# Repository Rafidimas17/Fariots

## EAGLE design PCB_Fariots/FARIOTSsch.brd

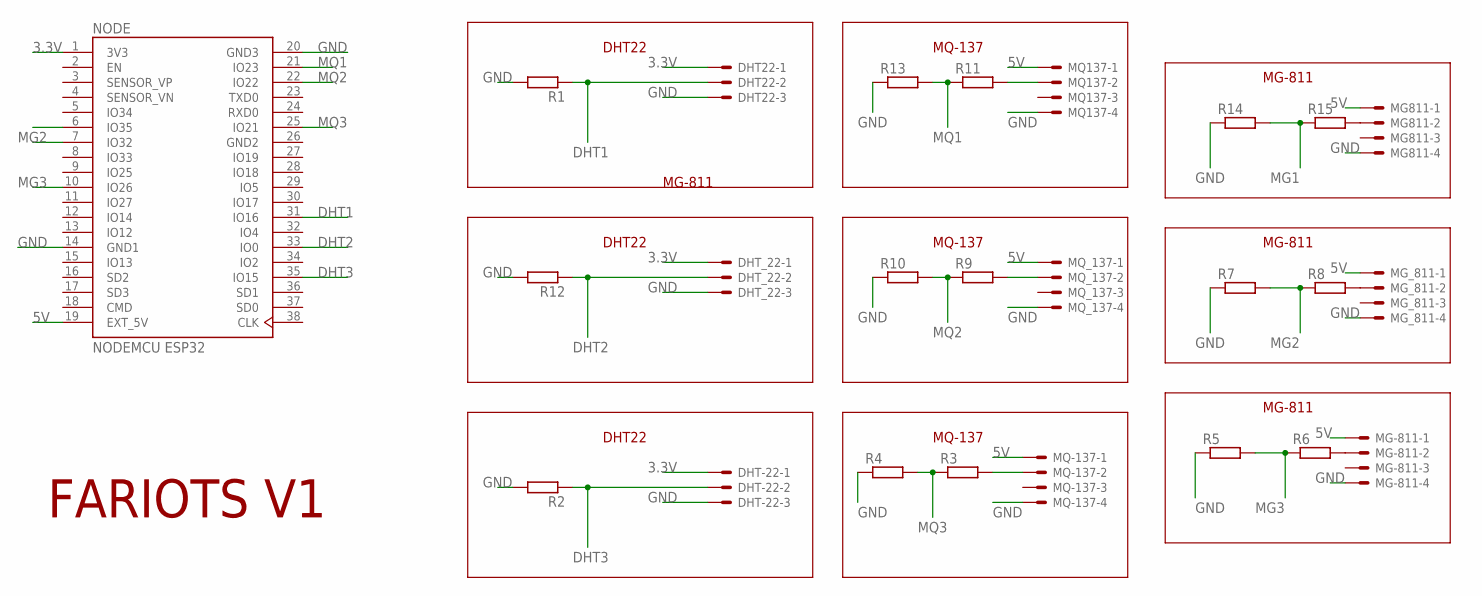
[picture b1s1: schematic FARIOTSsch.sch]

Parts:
DHT22: C-GRID-03-70543; 70543-03
DHT-22: C-GRID-03-70543; 70543-03
DHT_22: C-GRID-03-70543; 70543-03
MG811: C-GRID-04-70543; 70543-04
MG-811: C-GRID-04-70543; 70543-04
MG_811: C-GRID-04-70543; 70543-04
MQ137: C-GRID-04-70543; 70543-04
MQ-137: C-GRID-04-70543; 70543-04
MQ_137: C-GRID-04-70543; 70543-04
NODE: NODEMCU ESP32; MODULE_ESP32-DEVKITC-32D
R1, R2, R3, R4, R5, R6, R7, R8, R9, R10, R11, R12, R13, R14, R15: R-EU_0204/7; 0204/7

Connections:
3.3V: DHT22.1, DHT-22.1, DHT_22.1, NODE.1 (3V3)
5V: MG811.1, MG-811.1, MG_811.1, MQ137.1, MQ-137.1, MQ_137.1, NODE.19 (EXT_5V)
DHT1: DHT22.2, NODE.31 (IO16), R1.1
DHT2: DHT_22.2, NODE.33 (IO0), R12.1
DHT3: DHT-22.2, NODE.35 (IO15), R2.1
GND: DHT22.3, DHT-22.3, DHT_22.3, MG811.4, MG-811.4, MG_811.4, MQ137.4, MQ-137.4, MQ_137.4, NODE.14 (GND1), NODE.20 (GND3), R1.2, R2.2, R4.1, R5.1, R7.1, R10.1, R12.2, R13.1, R14.1
GND2: NODE.26 (GND2)
MG1: NODE.6 (IO35), R14.2, R15.1
MG2: NODE.7 (IO32), R7.2, R8.1
MG3: NODE.10 (IO26), R5.2, R6.1
MQ1: NODE.21 (IO23), R11.1, R13.2
MQ2: NODE.22 (IO22), R9.1, R10.2
MQ3: NODE.25 (IO21), R3.1, R4.2
unnamed: MG-811.2, R6.2
unnamed: MQ-137.2, R3.2
unnamed: MG_811.2, R8.2
unnamed: MQ_137.2, R9.2
unnamed: MQ137.2, R11.2
unnamed: MG811.2, R15.2

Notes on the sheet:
MG-811
MQ-137
DHT22
FARIOTS V1

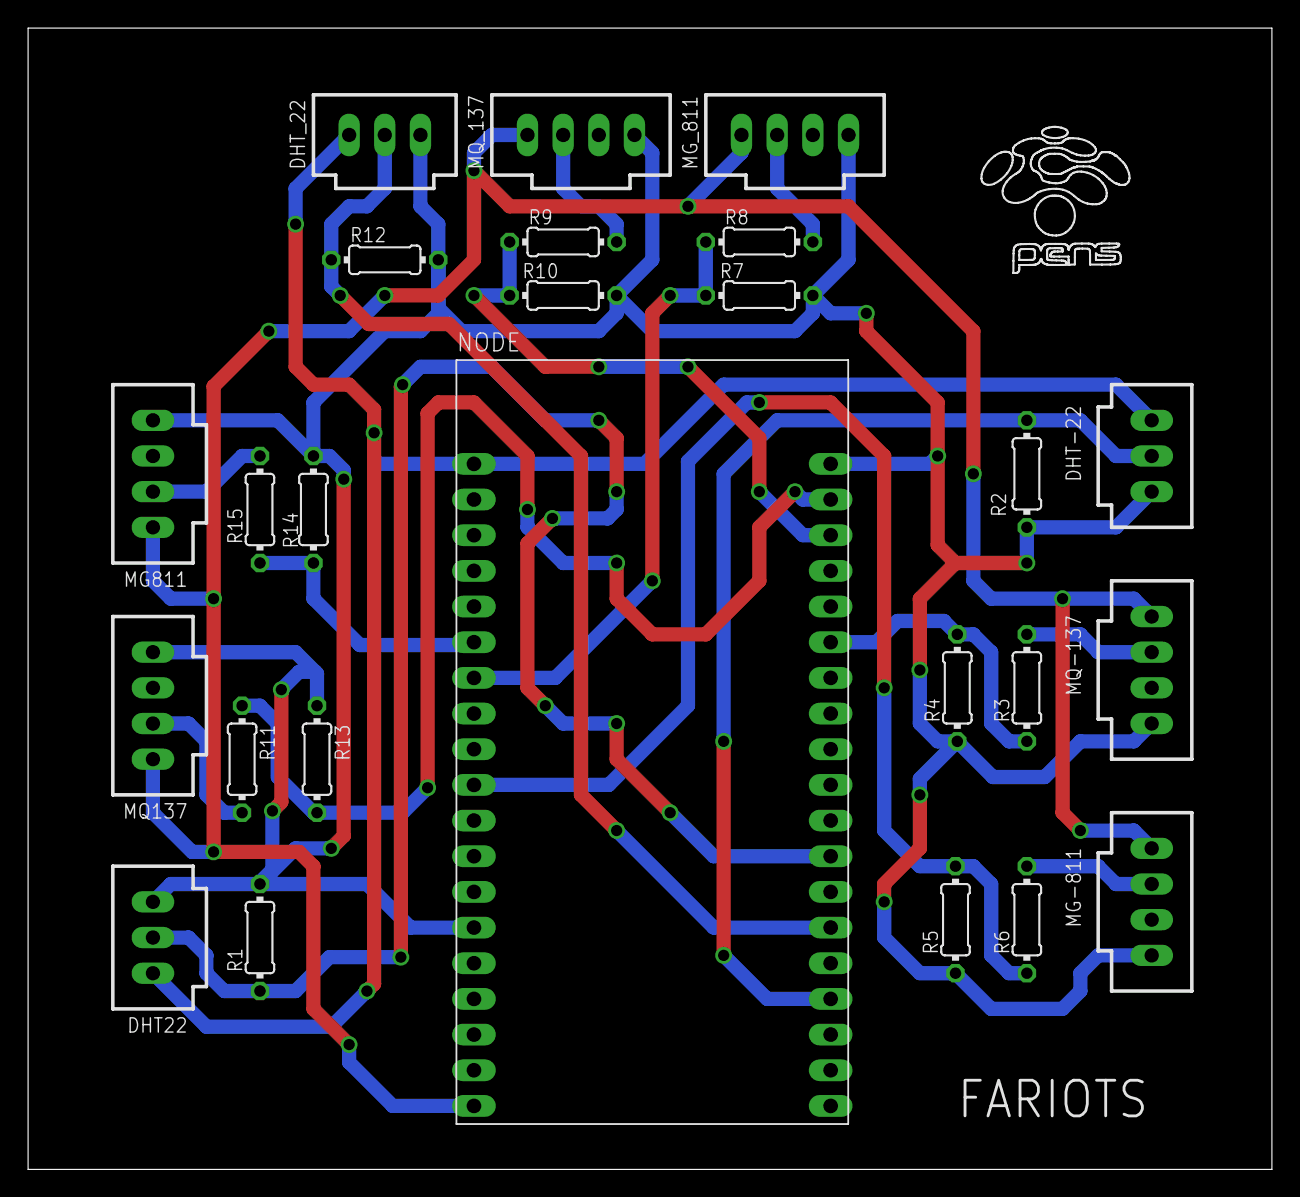
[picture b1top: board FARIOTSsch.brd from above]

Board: 2 copper layers, 88.6 x 81.3 mm, 25 parts (0 on the bottom side), 18 nets.

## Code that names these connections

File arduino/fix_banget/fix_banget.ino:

#include <WiFi.h>
#include "CO2Sensor.h"
#include <DHT.h>

//sediakan var untuk DHT
#define DHTPIN1 16
#define DHTPIN2 0
#define DHTPIN3 15
#define DHTTYPE DHT22
#define RL 47  //The value of resistor RL is 47K
#define m -0.263 //Enter calculated Slope 
#define b 0.42 //Enter calculated intercept
#define Ro 20 //Enter found Ro value
#define AN_Pot1    34 //Sensor is connected to 34
#define AN_Pot2    33 //Sensor is connected to 33
#define AN_Pot3    25 //Sensor is connected to 25

CO2Sensor co2Sensor(35, 0.99, 100);
CO2Sensor co2Sensor2(32, 0.99, 100);
CO2Sensor co2Sensor3(26, 0.99, 100);
//sediakan sebuah object untuk DHT22
DHT dht1(DHTPIN1, DHTTYPE);
DHT dht2(DHTPIN2, DHTTYPE);
DHT dht3(DHTPIN3, DHTTYPE);
const char* ssid     = "Aay";
const char* password = "hahgimana";
const char* host = "fariots.com";

void setup()
{
  dht1.begin();
  dht2.begin();
  dht3.begin();
  co2Sensor.calibrate();
  co2Sensor2.calibrate();
  co2Sensor3.calibrate();
  Serial.begin(115200);

  // We start by connecting to a WiFi network

//  Serial.println();
//  Serial.println();
//  Serial.print("Connecting to ");
//  Serial.println(ssid);

  WiFi.begin(ssid, password);

  while (WiFi.status() != WL_CONNECTED) {
    delay(500);
//    Serial.print(".");
  }

//  Serial.println("");
//  Serial.println("WiFi connected");
//  Serial.println("IP address: ");
//  Serial.println(WiFi.localIP());
}



void loop()
{
//mq1
  float VRL; //Voltage drop across the MQ sensor
  float Rs; //Sensor resistance at gas concentration 
  float ratio; //Define variable for ratio

  VRL = analogRead(AN_Pot1)*(5.0/1023.0); //Measure the voltage drop and convert to 0-5V
  Rs = ((5.0*RL)/VRL)-RL; //Use formula to get Rs value
  ratio = Rs/Ro;  // find ratio Rs/Ro

//mq2
  float VRL2; //Voltage drop across the MQ sensor
  float Rs2; //Sensor resistance at gas concentration 
  float ratio2; //Define variable for ratio

  VRL2 = analogRead(AN_Pot2)*(5.0/1023.0); //Measure the voltage drop and convert to 0-5V
  Rs2 = ((5.0*RL)/VRL2)-RL; //Use formula to get Rs value
  ratio2 = Rs2/Ro;  // find ratio Rs/Ro

  //mq3
  float VRL3; //Voltage drop across the MQ sensor
  float Rs3; //Sensor resistance at gas concentration 
  float ratio3; //Define variable for ratio

  VRL3 = analogRead(AN_Pot3)*(5.0/1023.0); //Measure the voltage drop and convert to 0-5V
  Rs3 = ((5.0*RL)/VRL3)-RL; //Use formula to get Rs value
  ratio3 = Rs3/Ro;  // find ratio Rs/Ro
  
  float temp = dht1.readTemperature();
  float humd = dht1.readHumidity();
  float amonia = pow(10, ((log10(ratio) - b) / m));
  float carbon = co2Sensor.read();
  float temp1 = dht2.readTemperature();
  float humd1 = dht2.readHumidity();
  float amonia1 = pow(10, ((log10(ratio2) - b) / m));
  float carbon1 = co2Sensor2.read();
  float temp2 = dht3.readTemperature();
  float humd2 = dht3.readHumidity();
  float amonia2 = pow(10, ((log10(ratio3) - b) / m));
  float carbon2 = co2Sensor3.read();
  
  Serial.print("Humidity: ");
  Serial.print(humd1);
  Serial.print(" %\t");
  Serial.print("Temperature: ");
  Serial.print(temp1);
  Serial.println(" *C");
  Serial.print("Amonia: ");
  Serial.print(amonia);
  Serial.println(" ppm");
  Serial.print("Humidity: ");
  Serial.print(humd1);
  Serial.print(" %\t");
  Serial.print("Temperature: ");
  Serial.print(temp1);
  Serial.println(" *C");
  Serial.print("Amonia: ");
  Serial.print(amonia1);
  Serial.println(" ppm");
  Serial.print("Humidity: ");
  Serial.print(humd2);
  Serial.print(" %\t");
  Serial.print("Temperature: ");
  Serial.print(temp2);
  Serial.println(" *C");
  Serial.print("Amonia: ");
  Serial.print(amonia2);
  Serial.println(" ppm");
  delay(3000);
  
Serial.println("------------Kirim Data-----------------");
   WiFiClient client;
     const int httpPort =80;
     if (!client.connect(host, httpPort)) {
        Serial.println("Koneksi host gagal");
        return;
     }
   
      String url = "/Fariots/setup.php?temperature=";
      url = url+ temp+"&humidity="+humd+"&amonia="+amonia+"&carbon="+carbon+"&temperature1="+temp1+"&humidity1="+humd1+"&amonia1="+amonia1+"&carbon1="+carbon1+
      "&temperature2="+temp2+"&humidity2="+humd2+"&amonia2="+amonia2+"&carbon2="+carbon2;
      Serial.print("Requesting URL: ");
      Serial.println(url);

      client.print(String("GET ") + url + " HTTP/1.1\r\n" +
                   "Host: " + host + "\r\n" +
                   "Connection: close\r\n\r\n");
      unsigned long timeout = millis();
      while (client.available() == 0) {
        if (millis() - timeout > 1000) {
          Serial.println(" Client Timeout!!!");
          client.stop();
          return;
        }
      }

      while (client.available()) {
        String line = client.readStringUntil('\r');
        Serial.print(line);
      }
    
      Serial.println();
      Serial.println("Menutup koneksi host");
}

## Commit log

2022-09-18 second commit
